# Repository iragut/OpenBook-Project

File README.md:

# README - OpenBook E-Reader

## Introducere
OpenBook este un e-reader open-source construit în jurul microcontrollerului ESP32-C6, integrând un display e-paper de 7.5 inch, senzori de mediu (BME680), management al bateriei și interfețe precum Wi-Fi și USB-C. Acest document oferă o privire de ansamblu asupra designului hardware, componentelor utilizate și conexiunilor lor.

---

## Diagrama bloc

## Bill of Materials (BOM)
Tabelul de mai jos include componentele principale din BOM-ul furnizat, cu link-uri către Mouser și datasheet-uri unde sunt disponibile.

| **Componentă**         | **Valoare/Part Number**         | **Descriere**                              | **Furnizor (Mouser)**                                                                 | **Datasheet**                                                                                     |
|-------------------------|---------------------------------|--------------------------------------------|--------------------------------------------------------------------------------------|--------------------------------------------------------------------------------------------------|
| U2                     | ESP32-C6-WROOM-1-N8            | Microcontroller Wi-Fi 6, Bluetooth 5       | [Mouser](https://eu.mouser.com/ProductDetail/Espressif-Systems/ESP32-C6-WROOM-1-N8)  | [Datasheet](https://www.espressif.com/sites/default/files/documentation/esp32-c6-wroom-1_datasheet_en.pdf) |
| U1                     | W25Q512JVEIQ                   | 512Mb Flash SPI                            | [Mouser](https://eu.mouser.com/ProductDetail/Winbond/W25Q512JVEIQ)                   | [Datasheet](https://www.winbond.com/resource-files/W25Q512JV%20RevD%2004082020.pdf)              |
| S                      | BME680                         | Senzor temperatură, umiditate, presiune    | [Mouser](https://eu.mouser.com/ProductDetail/Bosch-Sensortec/BME680)                 | [Datasheet](https://www.bosch-sensortec.com/media/boschsensortec/downloads/datasheets/bst-bme680-ds001.pdf) |
| U3                     | DS3231SN#                      | RTC I2C                                    | [Mouser](https://eu.mouser.com/ProductDetail/Analog-Devices/DS3231SN)                | [Datasheet](https://www.analog.com/media/en/technical-documentation/data-sheets/DS3231.pdf)       |
| U4                     | MAX17048G+T10                  | Fuel Gauge I2C                             | [Mouser](https://eu.mouser.com/ProductDetail/Analog-Devices/MAX17048G+T10)           | [Datasheet](https://www.analog.com/media/en/technical-documentation/data-sheets/MAX17048.pdf)     |
| U5                     | MCP73831T-2ACI/OT              | Încărcător Li-Po USB-C                     | [Mouser](https://eu.mouser.com/ProductDetail/Microchip-Technology/MCP73831T-2ACI-OT) | [Datasheet](https://ww1.microchip.com/downloads/en/DeviceDoc/20001984G.pdf)                     |
| J2                     | USB4110-GF-A                   | Conector USB-C                             | [Mouser](https://eu.mouser.com/ProductDetail/GCT/USB4110-GF-A)                       | [Datasheet](https://www.gct.co/connector/usb4110)                                               |
| BOOT_BUTTON            | EVQPUJ02K                      | Buton tactil                               | [Mouser](https://eu.mouser.com/ProductDetail/Panasonic/EVQ-PUJ02K)                   | [Datasheet](https://www.panasonic.com/global/industrial-components/switches/light-touch/evqpuj02k.pdf) |
| C3                     | 100uF TANT (F910J107MBAAJ6)    | Condensator polarizat                      | [Mouser](https://eu.mouser.com/ProductDetail/KYOCERA-AVX/F910J107MBAAJ6)             | [Datasheet](https://www.kyocera-avx.com/products/tantalum/)                                     |
| IC4                    | XC6220A331MR-G                 | LDO Regulator                              | [Mouser](https://eu.mouser.com/ProductDetail/Torex/XC6220A331MR-G)                   | [Datasheet](https://www.torexsemi.com/file/xc6220/XC6220.pdf)                                   |

---

## Funcționalitate Hardware

### Microcontroller ESP32-C6-WROOM-1-N8
- **Rol**: Procesare centrală, conectivitate Wi-Fi 6 și Bluetooth 5, control al perifericelor.
- **Interfețe**:
  - SPI: Display e-paper, Flash (W25Q512JVEIQ), Micro SD.
  - I2C: BME680, MAX17048, DS3231.
  - GPIO: Butoane, LED, pini de control display.
  - UART: Debugging și extensii.
- **Specificații**: 160MHz, 512KB SRAM, 8MB Flash integrat.

### Display E-Paper
- **Specificații**: 7.5 inch, 800x480, contrast 8:1, SPI 4-wire.
- **Conexiune**: MOSI, MISO, SCK, CS + DC, RST, BUSY.
- **Consum**: <50mA în refresh, aproape 0 în standby.

### Senzor BME680
- **Funcție**: Măsoară temperatura (±1°C), umiditatea (±3%), presiunea (±1 hPa) și calitatea aerului (eCO2, TVOC).
- **Interfață**: I2C la 400kHz.
- **Consum**: <1mA activ, <1µA în sleep.

### Management Baterie
- **Baterie**: 2500mAh Li-Po, 3.7V.
- **Încărcare**: MCP73831 prin USB-C (1A max).
- **Monitorizare**: MAX17048 prin I2C.
- **Consum**: <50µA în deep sleep.

### Butoane
- Trei butoane tactile (Panasonic EVQPUJ02K) pentru navigare, cu rezistențe pull-up de 10K.

### USB-C
- **Rol**: Încărcare (5V/1A) și transfer date (USB 2.0).
- **Protecție**: ESD diodes (USBLC6-2SC6Y).

### Calcul Consum Energie
- **Activ (Wi-Fi + Display Refresh)**: ~150mA.
- **Citire (Display static)**: ~10mA.
- **Deep Sleep**: <50µA.
- **Autonomie estimată**: ~1 săptămână (2500mAh / 10mA medie = ~250 ore).

---

## Pini ESP32-C6 Utilizați

| **Pin ESP32-C6** | **Funcție**         | **Componentă**         | **Motiv**                                      |
|-------------------|---------------------|------------------------|------------------------------------------------|
| GPIO0            | BOOT_BUTTON         | Buton                  | Detectare mod boot la pornire                  |
| GPIO1            | RESET_BUTTON        | Buton                  | Reset manual al dispozitivului                 |
| GPIO2            | CHANGE_BUTTON       | Buton                  | Navigare meniuri                               |
| GPIO3            | EPD_CS              | Display E-Paper        | Chip Select pentru SPI                         |
| GPIO4            | EPD_DC              | Display E-Paper        | Data/Command control                           |
| GPIO5            | EPD_RST             | Display E-Paper        | Reset display                                  |
| GPIO6            | EPD_BUSY            | Display E-Paper        | Detectare stare refresh                        |
| GPIO7            | SPI_MOSI            | Display, Flash, SD     | Master Out Slave In (SPI)                      |
| GPIO8            | SPI_MISO            | Display, Flash, SD     | Master In Slave Out (SPI)                      |
| GPIO9            | SPI_SCK             | Display, Flash, SD     | Clock SPI                                      |
| GPIO10           | FLASH_CS            | W25Q512JVEIQ           | Chip Select pentru Flash                       |
| GPIO11           | SD_CS               | Micro SD               | Chip Select pentru SD                          |
| GPIO12           | I2C_SDA             | BME680, MAX17048, DS3231 | Date I2C                                     |
| GPIO13           | I2C_SCL             | BME680, MAX17048, DS3231 | Clock I2C                                    |
| GPIO14           | CHG_LED             | LED                    | Indicare status încărcare                      |
| GPIO15           | UART_TX             | Debugging              | Transmitere date serial                        |
| GPIO16           | UART_RX             | Debugging              | Recepție date serial                           |
| GPIO17           | USB_D+              | USB-C                  | Linie date USB pozitivă                        |
| GPIO18           | USB_D-              | USB-C                  | Linie date USB negativă                        |

**Notă**: Pinii sunt alocați conform specificațiilor ESP32-C6 și cerințelor ERD/PRD. Unii pini pot fi multifuncționali (ex. GPIO/SPI).

---

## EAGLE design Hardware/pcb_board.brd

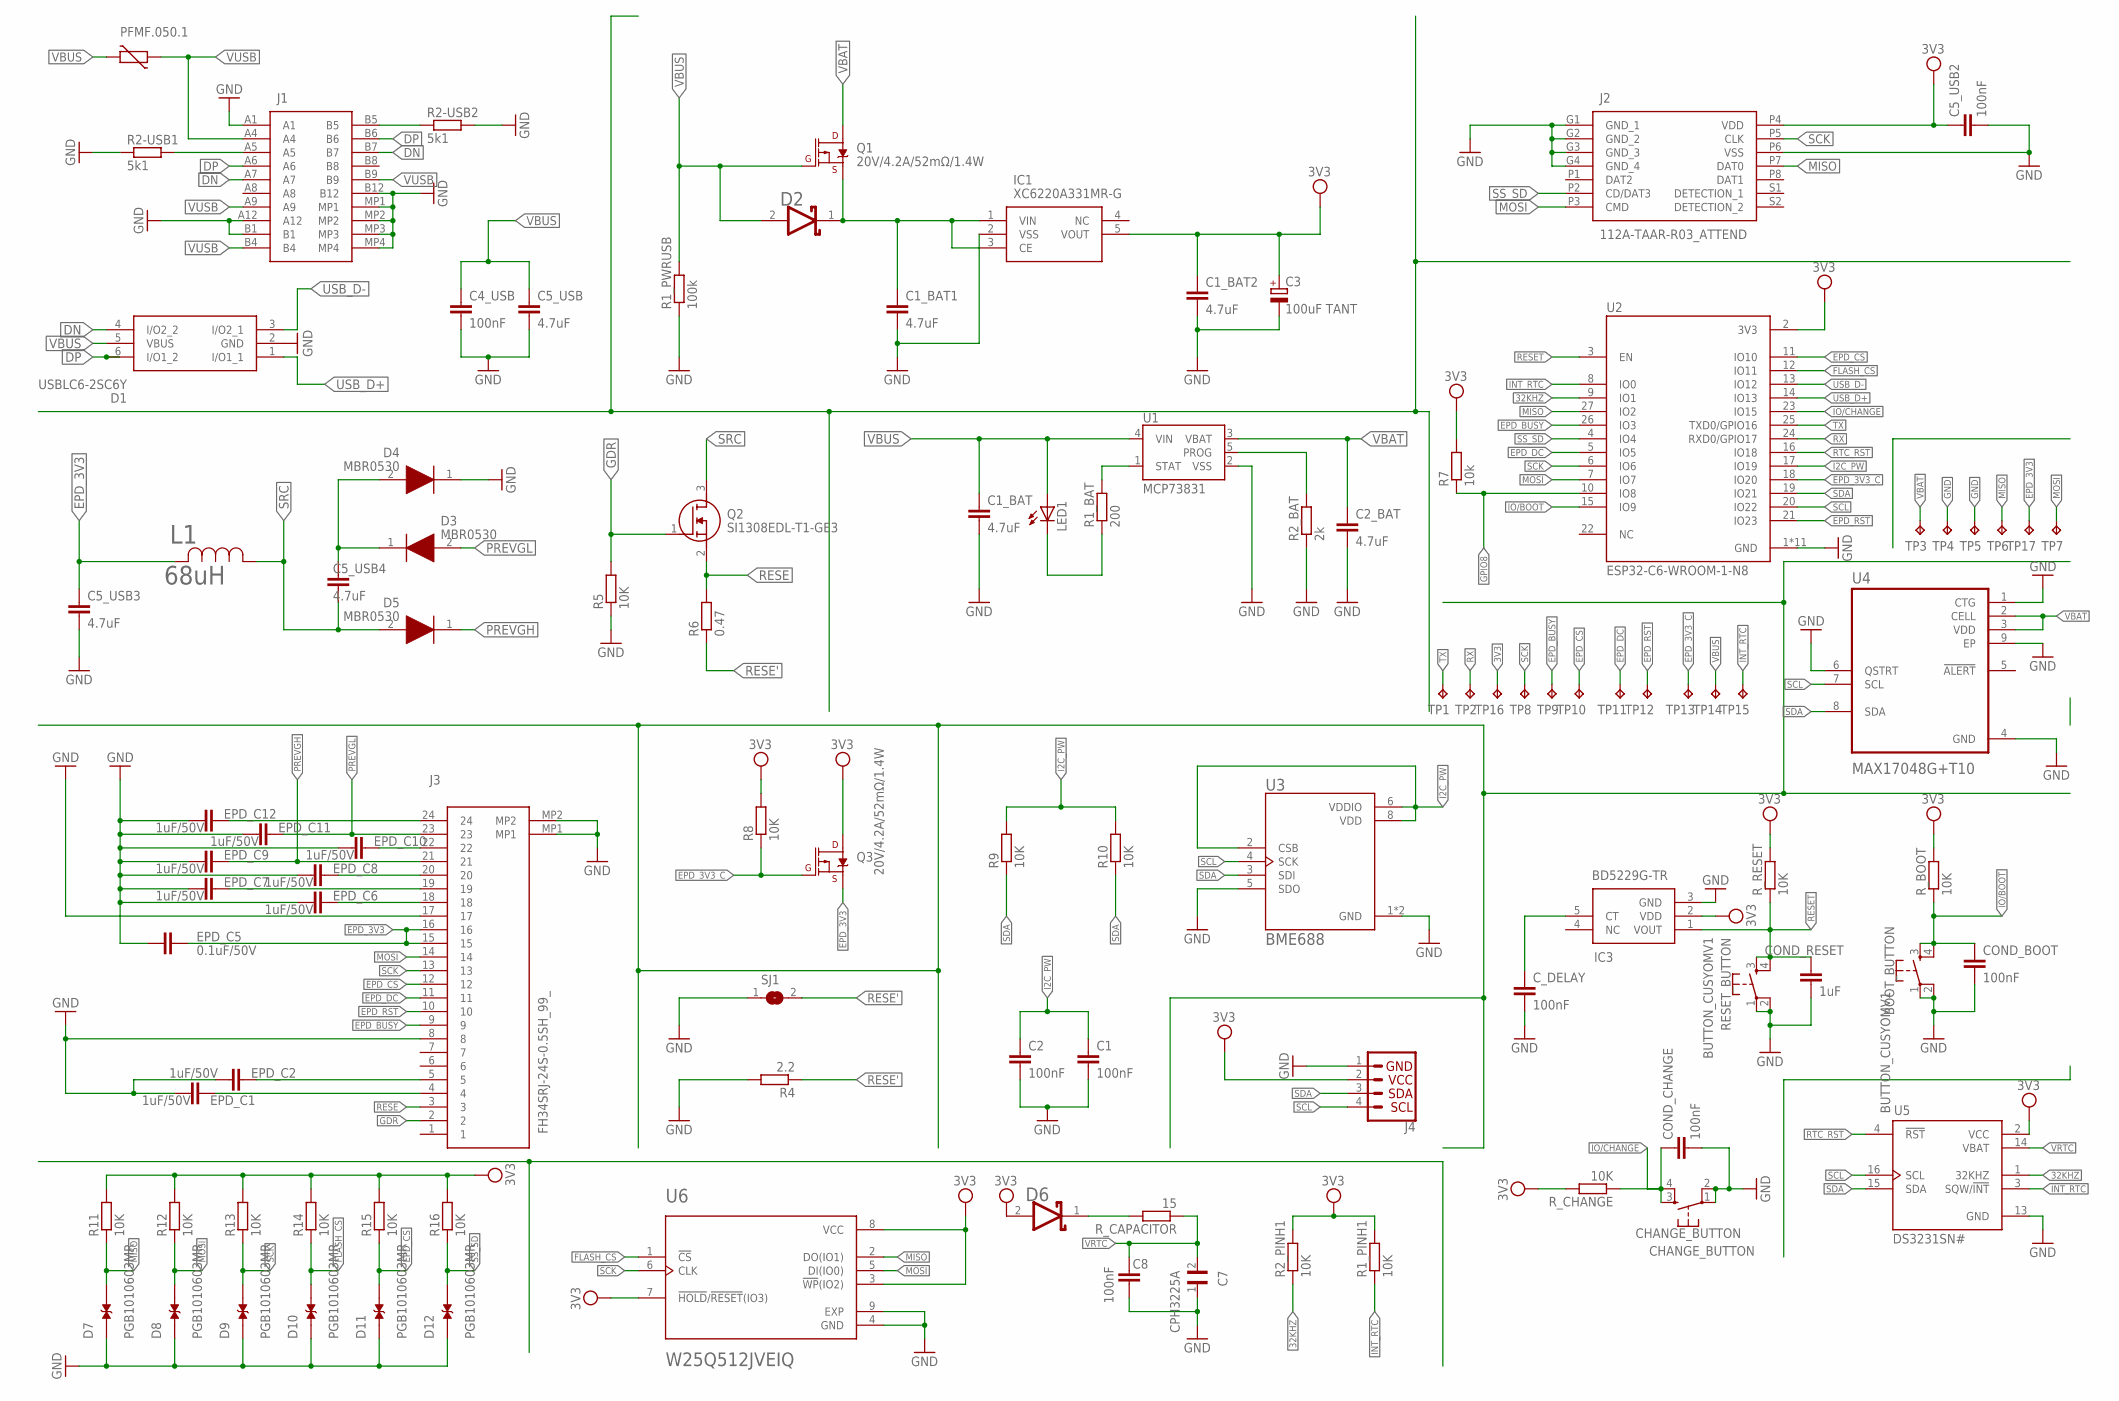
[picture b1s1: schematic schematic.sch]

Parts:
BOOT_BUTTON: BUTTON_CUSYOMV1; MYBUTTON
C1, C2, C4_USB, C5_USB2, C8: 100nF; ESP32_WROVER_EAGLE-LTSPICE_C0402
C1_BAT, C1_BAT1, C1_BAT2, C2_BAT, C5_USB, C5_USB3, C5_USB4: 4.7uF; ESP32_WROVER_EAGLE-LTSPICE_C0402
C3: 100uF TANT; RCL_CT3528
C7: CPH3225A; CAPCP3225X100N
CHANGE_BUTTON: CHANGE_BUTTON; MYBUTTON
COND_BOOT: 100nF; ESP32_WROVER_EAGLE-LTSPICE_C0402
COND_CHANGE: 100nF; ESP32_WROVER_EAGLE-LTSPICE_C0402
COND_RESET: 1uF; ESP32_WROVER_EAGLE-LTSPICE_C0402
C_DELAY: 100nF; ESP32_WROVER_EAGLE-LTSPICE_C0402
D1: USBLC6-2SC6Y; SOT95P280X145-6N
D2: SD0805S020S1R0; ESP32_WROVER_AVX---SD0805S020S1R0_AVX_SD0805S020S1R0_0
D3, D4, D5: MBR0530; SOD3716X135N
D6: ESP32_WROVER_AVX---SD0805S020S1R0_AVX_SD0805S020S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; ESP32_WROVER_AVX---SD0805S020S1R0_AVX_SD0805S020S1R0_0
D7, D8, D9, D10, D11, D12: PGB1010603MR; DIOC1608X36N
EPD_C1, EPD_C2, EPD_C6, EPD_C7, EPD_C8, EPD_C9, EPD_C10, EPD_C11, EPD_C12: 1uF/50V; ESP32_WROVER_EAGLE-LTSPICE_C0402
EPD_C5: 0.1uF/50V; ESP32_WROVER_EAGLE-LTSPICE_C0402
IC1: XC6220A331MR-G; SOT95P280X120-5N
IC3: BD5229G-TR; SOT95P280X125-5N
J1: SAMACSYS_PARTS_USB4110-GF-A; SAMACSYS_PARTS_USB4110GFA
J2: 112A-TAAR-R03_ATTEND; 112ATAARR03ATTEND
J3: FH34SRJ-24S-0.5SH_99_; FH34SRJ24S05SH99
J4: QWIIC_RIGHT_ANGLE; JST04_1MM_RA
L1: 68uH; IND_4828-WE-TPC_WRE
LED1: ADAFRUIT_LEDCHIP-LED0603; ADAFRUIT_CHIP-LED0603
PFMF.050.1: ESP32C6_VARISTORCN1812; ESP32C6_VARISTOR_CT/CN1812
Q1, Q3: 20V/4.2A/52mΩ/1.4W; ESP32_WROVER_SPARKFUN-DISCRETESEMI_SOT23-3
Q2: SI1308EDL-T1-GE3; SOT65P210X110-3N
R1_BAT: 200; ESP32_WROVER_EAGLE-LTSPICE_R0402
R1_PINH1, R2_PINH1, R5, R8, R9, R10, R11, R12, R13, R14, R15, R16: 10K; ESP32_WROVER_EAGLE-LTSPICE_R0402
R1_PWRUSB: 100k; ESP32_WROVER_EAGLE-LTSPICE_R0402
R2-USB1, R2-USB2: 5k1; ESP32_WROVER_EAGLE-LTSPICE_R0402
R2_BAT: 2k; ESP32_WROVER_EAGLE-LTSPICE_R0402
R4: 2.2; ESP32_WROVER_EAGLE-LTSPICE_R0402
R6: 0.47; ESP32_WROVER_EAGLE-LTSPICE_R0402
R7: 10k; ESP32_WROVER_EAGLE-LTSPICE_R0402
RESET_BUTTON: BUTTON_CUSYOMV1; MYBUTTON
R_BOOT: 10K; ESP32_WROVER_EAGLE-LTSPICE_R0402
R_CAPACITOR: 15; ESP32_WROVER_EAGLE-LTSPICE_R0402
R_CHANGE: 10K; ESP32_WROVER_EAGLE-LTSPICE_R0402
R_RESET: 10K; ESP32_WROVER_EAGLE-LTSPICE_R0402
SJ1: SJ
TP1, TP2, TP3, TP4, TP5, TP6, TP7, TP8, TP9, TP10, TP11, TP12, TP13, TP14, TP15, TP16, TP17: TPTP20R; TP20R
U1: MCP73831; ESP32_WROVER_SPARKFUN-IC-POWER_SOT23-5
U2: ESP32-C6-WROOM-1-N8; XCVR_ESP32-C6-WROOM-1-N8
U3: BME688; ESP32_WROVER_BME680_PSON80P300X300X100-8N
U4: MAX17048G+T10; SON50P200X200X80-9N
U5: DS3231SN#; SOIC127P1032X265-16N
U6: W25Q512JVEIQ; SON127P600X800X80-9N

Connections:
3V3: C1_BAT2.1, C3.+, C5_USB2.1, D6.2 (ANODE), IC1.5 (VOUT), IC3.2 (VDD), J2.P4 (VDD), J4.2, Q3.3 (D), R1_PINH1.2, R2_PINH1.2, R7.2, R8.2, R11.2, R12.2, R13.2, R14.2, R15.2, R16.2, R_BOOT.2, R_CHANGE.2, R_RESET.2, TP16.TP, U2.2 (3V3), U5.2 (VCC), U6.3 (!WP!(IO2)), U6.7 (!HOLD!/!RESET!(IO3)), U6.8 (VCC)
32KHZ: R2_PINH1.1, U2.9 (IO1), U5.1 (32KHZ)
DN: D1.4 (I/O2_2), J1.A7, J1.B7
DP: D1.6 (I/O1_2), J1.A6, J1.B6
EPD_3V3: C5_USB3.1, EPD_C5.1, J3.15, J3.16, L1.2, Q3.2 (S), TP17.TP
EPD_3V3_C: Q3.1 (G), R8.1, TP13.TP, U2.18 (IO20)
EPD_BUSY: J3.9, TP9.TP, U2.26 (IO3)
EPD_CS: D11.2, J3.12, R15.1, TP10.TP, U2.11 (IO10)
EPD_DC: J3.11, TP11.TP, U2.5 (IO5)
EPD_RST: J3.10, TP12.TP, U2.21 (IO23)
FLASH_CS: D10.2, R14.1, U2.12 (IO11), U6.1 (!CS)
GDR: J3.2, Q2.1 (G), R5.2
GND: BOOT_BUTTON.1, BOOT_BUTTON.2, C1.2, C1_BAT.2, C1_BAT1.2, C1_BAT2.2, C2.2, C2_BAT.2, C3.-, C4_USB.2, C5_USB.2, C5_USB2.2, C5_USB3.2, C7.1, C8.2, CHANGE_BUTTON.1, CHANGE_BUTTON.2, COND_BOOT.2, COND_CHANGE.2, COND_RESET.2, C_DELAY.2, D1.2 (GND), D4.1 (K), D7.1, D8.1, D9.1, D10.1, D11.1, D12.1, EPD_C1.2, EPD_C2.2, EPD_C5.2, EPD_C6.2, EPD_C7.2, EPD_C8.2, EPD_C9.2, EPD_C10.2, EPD_C11.2, EPD_C12.2, IC1.2 (VSS), IC3.3 (GND), J1.A1, J1.A12, J1.B1, J1.B12, J1.MP1, J1.MP2, J1.MP3, J1.MP4, J2.G1 (GND_1), J2.G2 (GND_2), J2.G3 (GND_3), J2.G4 (GND_4), J2.P6 (VSS), J3.8, J3.17, J3.MP1, J3.MP2, J4.1, R1_PWRUSB.1, R2-USB1.1, R2-USB2.2, R2_BAT.1, R4.2, R5.1, RESET_BUTTON.1, RESET_BUTTON.2, SJ1.1, TP4.TP, TP5.TP, U1.2 (VSS), U2.1 (GND), U2.28 (GND), U2.29_1 (GND), U2.29_2 (GND), U2.29_3 (GND), U2.29_4 (GND), U2.29_5 (GND), U2.29_6 (GND), U2.29_7 (GND), U2.29_8 (GND), U2.29_9 (GND), U3.1 (GND), U3.5 (SDO), U3.7 (GND), U4.1 (CTG), U4.4 (GND), U4.6 (QSTRT), U4.9 (EP), U5.13 (GND), U6.4 (GND), U6.9 (EXP)
GPIO8: R7.1, U2.10 (IO8)
I2C_PW: C1.1, C2.1, R9.2, R10.2, U2.17 (IO19), U3.2 (CSB), U3.6 (VDDIO), U3.8 (VDD)
INT_RTC: R1_PINH1.1, TP15.TP, U2.8 (IO0), U5.3 (SQW/!INT)
IO/BOOT: BOOT_BUTTON.3, BOOT_BUTTON.4, COND_BOOT.1, R_BOOT.1, U2.15 (IO9)
IO/CHANGE: CHANGE_BUTTON.3, CHANGE_BUTTON.4, COND_CHANGE.1, R_CHANGE.1, U2.23 (IO15)
MISO: D7.2, J2.P7 (DAT0), R11.1, TP6.TP, U2.27 (IO2), U6.2 (DO(IO1))
MOSI: D8.2, J2.P3 (CMD), J3.14, R12.1, TP7.TP, U2.7 (IO7), U6.5 (DI(IO0))
unnamed: C1_BAT1.1, D2.1 (CATHODE), IC1.1 (VIN), IC1.3 (CE), Q1.2 (S)
unnamed: EPD_C12.1, J3.24
unnamed: R1_BAT.2, U1.1 (STAT)
unnamed: J1.B5, R2-USB2.1
unnamed: J1.A5, R2-USB1.2
unnamed: C5_USB4.1, D3.1 (K), D4.2 (A)
unnamed: LED1.C, R1_BAT.1
unnamed: R2_BAT.2, U1.5 (PROG)
unnamed: D6.1 (CATHODE), R_CAPACITOR.2
unnamed: EPD_C10.1, J3.22
unnamed: C_DELAY.1, IC3.5 (CT)
unnamed: EPD_C7.1, J3.19
unnamed: EPD_C8.1, J3.20
unnamed: EPD_C6.1, J3.18
unnamed: EPD_C2.1, J3.5
unnamed: EPD_C1.1, J3.4
PREVGH: D5.1 (K), EPD_C9.1, J3.21
PREVGL: D3.2 (A), EPD_C11.1, J3.23
RESE: J3.3, Q2.2 (S), R6.2
RESE': R4.1, R6.1, SJ1.2
RESET: COND_RESET.1, IC3.1 (VOUT), RESET_BUTTON.3, RESET_BUTTON.4, R_RESET.1, U2.3 (EN)
RTC_RST: U2.16 (IO18), U5.4 (!RST)
RX: TP2.TP, U2.24 (RXD0/GPIO17)
SCK: D9.2, J2.P5 (CLK), J3.13, R13.1, TP8.TP, U2.6 (IO6), U6.6 (CLK)
SCL: J4.4, U2.20 (IO22), U3.4 (SCK), U4.7 (SCL), U5.16 (SCL)
SDA: J4.3, R9.1, R10.1, U2.19 (IO21), U3.3 (SDI), U4.8 (SDA), U5.15 (SDA)
SRC: C5_USB4.2, D5.2 (A), L1.1, Q2.3 (D)
SS_SD: D12.2, J2.P2 (CD/DAT3), R16.1, U2.4 (IO4)
TX: TP1.TP, U2.25 (TXD0/GPIO16)
USB_D+: D1.1 (I/O1_1), U2.14 (IO13)
USB_D-: D1.3 (I/O2_1), U2.13 (IO12)
VBAT: C2_BAT.1, Q1.3 (D), TP3.TP, U1.3 (VBAT), U4.2 (CELL), U4.3 (VDD)
VBUS: C1_BAT.1, C4_USB.1, C5_USB.1, D1.5 (VBUS), D2.2 (ANODE), LED1.A, PFMF.050.1.2, Q1.1 (G), R1_PWRUSB.2, TP14.TP, U1.4 (VIN)
VRTC: C7.2, C8.1, R_CAPACITOR.1, U5.14 (VBAT)
VUSB: J1.A4, J1.A9, J1.B4, J1.B9, PFMF.050.1.1

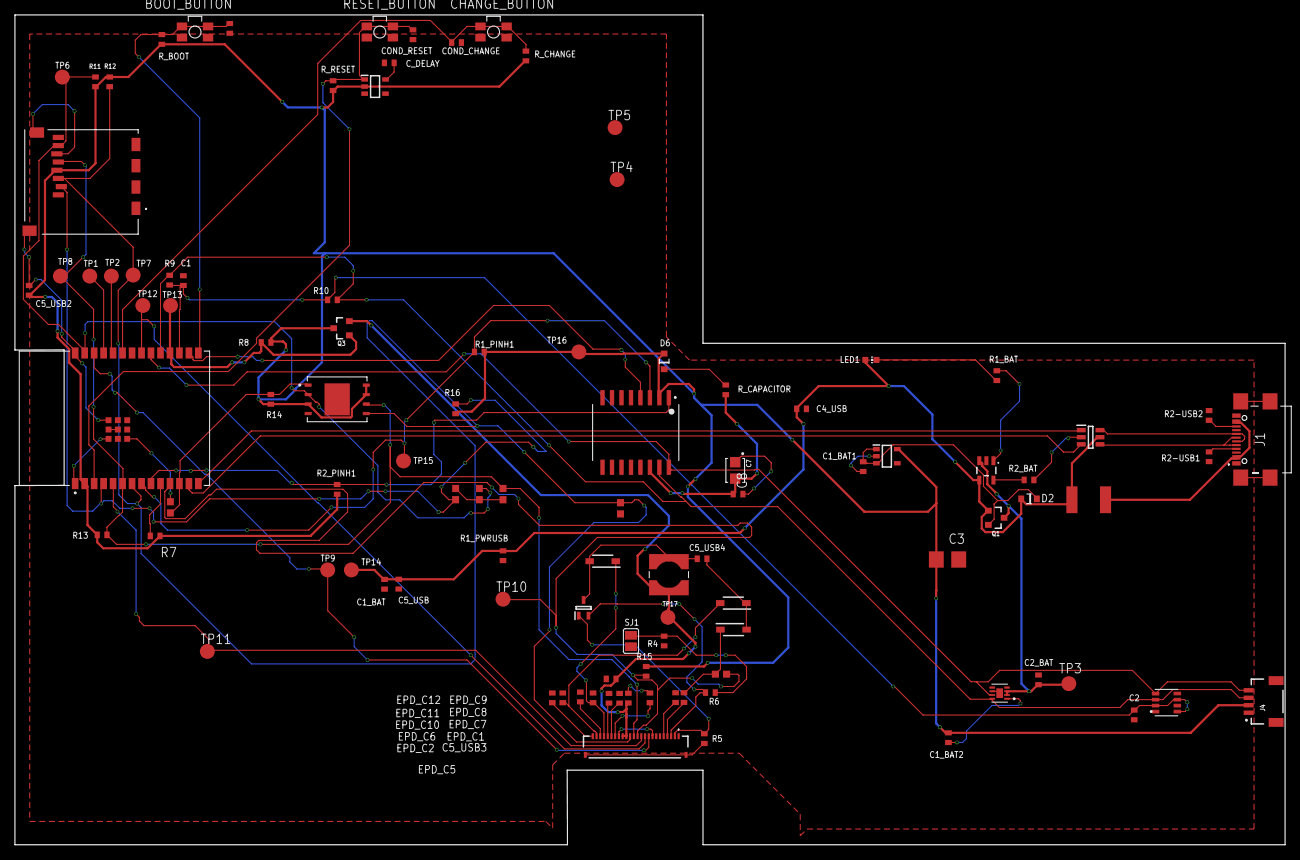
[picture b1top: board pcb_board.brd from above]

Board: 2 copper layers, 170.2 x 111.2 mm, 103 parts (0 on the bottom side), 55 nets.

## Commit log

2025-03-30 Create LICENSE
2025-04-05 add project
2025-04-12 Add diagram
2025-04-14 Resolve Issue 1 2 and add battery cable

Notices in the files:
parts and their libraries:
COPYRIGHT: Copyright (C) 2024 Ultra Librarian. All rights reserved.
